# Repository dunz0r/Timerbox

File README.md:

Timerbox
========

A small AVR-controlled timerbox

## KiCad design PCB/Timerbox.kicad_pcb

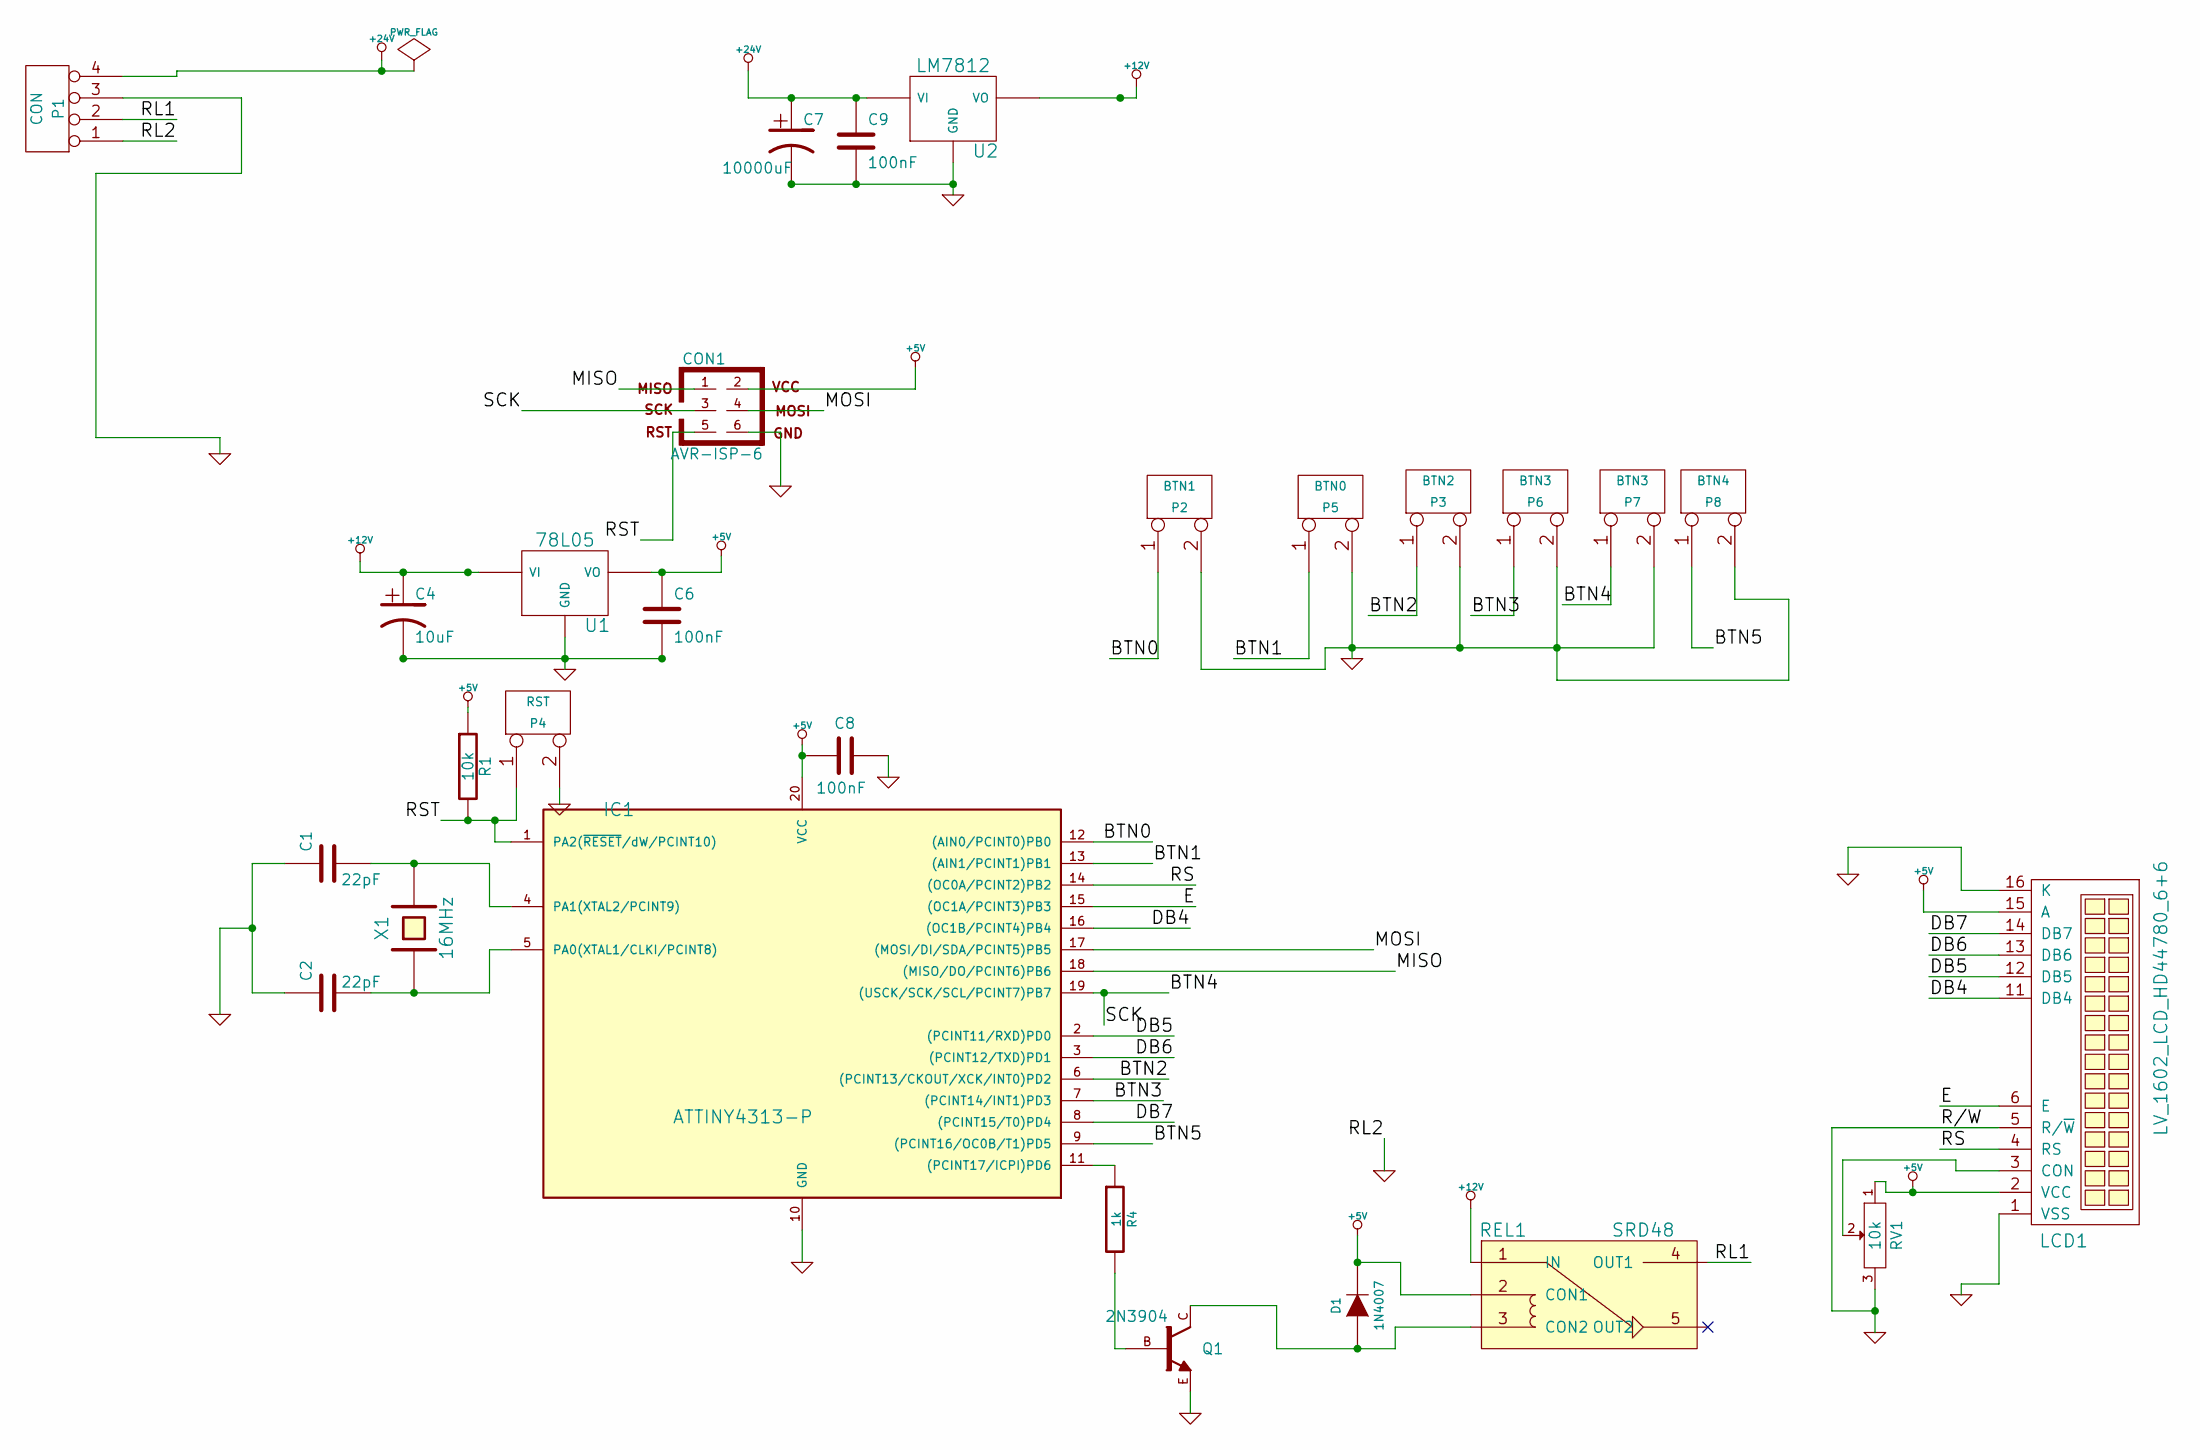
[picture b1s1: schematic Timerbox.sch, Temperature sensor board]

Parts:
C1, C2: 22pF
C4: 10uF
C6, C8, C9: 100nF
C7: 10000uF
CON1: AVR-ISP-6
D1: 1N4007
IC1: ATTINY4313-P; DIP20
LCD1: LV_1602_LCD_HD44780_6+6
P1: CON
P2: BTN1
P3: BTN2
P4: RST
P5: BTN0
P6, P7: BTN3
P8: BTN4
Q1: 2N3904
R1: 10k
R4: 1k
REL1: SRD48
RV1: 10k
U1: 78L05
U2: LM7812
X1: 16MHz

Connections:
+5V: C6.1, C8.1, CON1.2, D1.2 (K), IC1.20 (VCC), LCD1.2 (VCC), LCD1.15 (A), R1.1, REL1.2 (CON1), RV1.1, U1.VO
+12V: C4.1, REL1.1 (IN), U1.VI, U2.VO
+24V: C7.1, C9.1, P1.4, U2.VI
/BTN0: IC1.12 ((AIN0/PCINT0)PB0), P2.1
/BTN1: IC1.13 ((AIN1/PCINT1)PB1), P5.1
/BTN2: IC1.6 ((PCINT13/CKOUT/XCK/INT0)PD2), P3.1
/BTN3: IC1.7 ((PCINT14/INT1)PD3), P6.1
/BTN4: CON1.3, IC1.19 ((USCK/SCK/SCL/PCINT7)PB7), P7.1
/BTN5: IC1.9 ((PCINT16/OC0B/T1)PD5), P8.1
/DB4: IC1.16 ((OC1B/PCINT4)PB4), LCD1.11 (DB4)
/DB5: IC1.2 ((PCINT11/RXD)PD0), LCD1.12 (DB5)
/DB6: IC1.3 ((PCINT12/TXD)PD1), LCD1.13 (DB6)
/DB7: IC1.8 ((PCINT15/T0)PD4), LCD1.14 (DB7)
/E: IC1.15 ((OC1A/PCINT3)PB3), LCD1.6 (E)
/MISO: CON1.1, IC1.18 ((MISO/DO/PCINT6)PB6)
/MOSI: CON1.4, IC1.17 ((MOSI/DI/SDA/PCINT5)PB5)
/RL1: P1.2, REL1.4 (OUT1)
/RS: IC1.14 ((OC0A/PCINT2)PB2), LCD1.4 (RS)
/RST: CON1.5, IC1.1 (PA2(~RESET~/dW/PCINT10)), P4.1, R1.2
GND: C1.1, C2.1, C4.2, C6.2, C7.2, C8.2, C9.2, CON1.6, IC1.10 (GND), LCD1.1 (VSS), LCD1.5 (R/~W), LCD1.16 (K), P1.1, P1.3, P2.2 (PM), P3.2 (PM), P4.2 (PM), P5.2 (PM), P6.2 (PM), P7.2 (PM), P8.2 (PM), Q1.E, RV1.3, U1.GND, U2.GND
unnamed: IC1.11 ((PCINT17/ICPI)PD6), R4.1
unnamed: LCD1.3 (CON), RV1.2
unnamed: Q1.B, R4.2
unnamed: C1.2, IC1.4 (PA1(XTAL2/PCINT9)), X1.2
unnamed: C2.2, IC1.5 (PA0(XTAL1/CLKI/PCINT8)), X1.1
unnamed: D1.1 (A), Q1.C, REL1.3 (CON2)

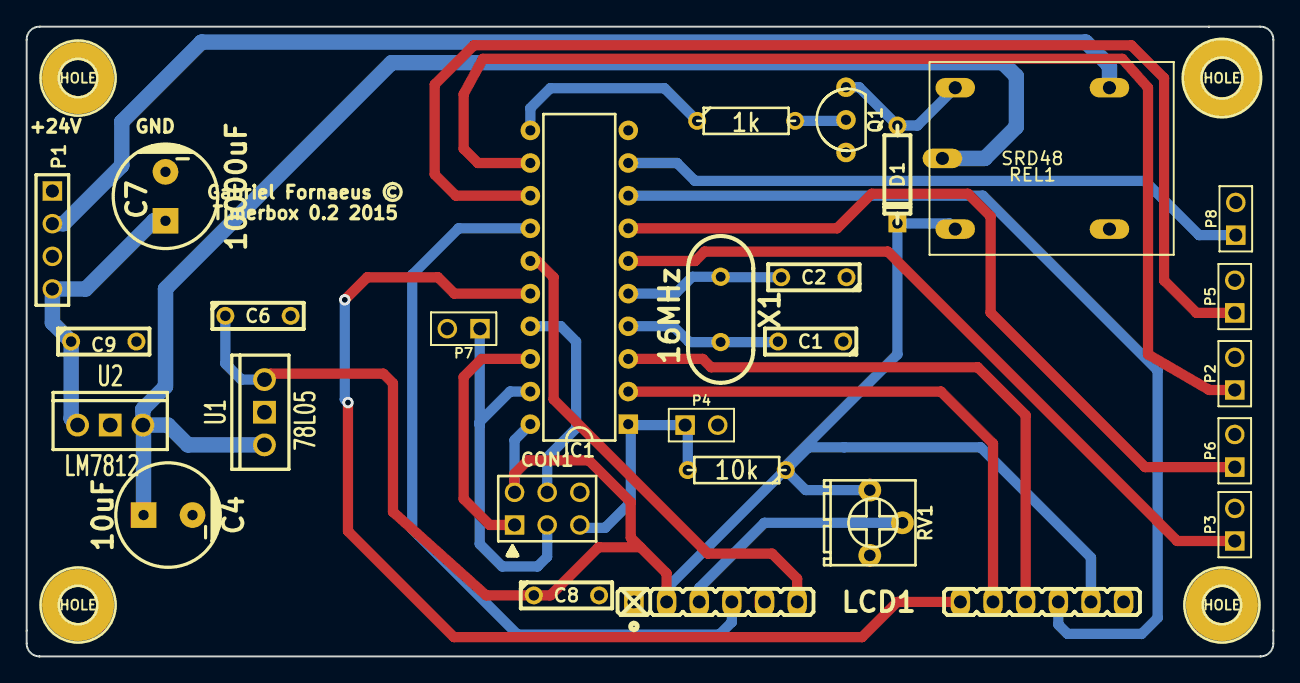
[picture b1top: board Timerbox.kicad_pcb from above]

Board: 2 copper layers, 97.0 x 49.0 mm, 31 parts (0 on the bottom side), 26 nets.

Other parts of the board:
HOLE: Val**; HOLE_30
HOLE#2, HOLE#3, HOLE#4: Val**; HOLE_28

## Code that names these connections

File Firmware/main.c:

/*
 * File Name : main.c
 * Purpose : Blink an LED
 * Creation Date : 01-05-2013
 * Last Modified : mån 15 sep 2014 23:47:50
 * Created By : Gabriel Fornaeus, <gf@hax0r.se>
 *
 */

#include <avr/io.h>
#include <util/delay.h>
#include <avr/interrupt.h>
#include <stdio.h>
#include "lib/buttons.h"
#include "lib/hd44780.h"

int main (void) {
	// Clear interrupts during setup phase
	cli();
	lcd_init();
	lcd_clrscr();
	lcd_gotoxy(0,1);
	lcd_puts("http://hax0r.se");
	// Set up as output
	DDRD |= (1 << PD5) | (1 << PD6);

	// Set up inputs
	DDRD &= ~(1 << PD2);
	DDRD &= ~(1 << PD3);
	// Enable pullups
	PORTD |= (1 << PD2);
	PORTD |= (1 << PD3);

	// initialize and enale interrupts
	initInterrupts();
	sei();

	// Go to zero position
	lcd_gotoxy(0,0);
	_delay_ms(1000);
	lcd_clrscr();
	for(;;) {
		PORTD ^= (1 << PD5);
		_delay_ms(200);
	}
}

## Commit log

2014-09-08 Gitignore and netlist
2014-09-15 Formatting edits
2014-09-15 Moved libraries
2014-09-15 Interrupts moved to library
2014-09-15 Interrupts library
2014-09-15 Clarifying comments
2014-09-15 Renamed interrupts to encoders
2014-09-15 Settings file for encoders added
2014-10-07 Makefile updated
2014-12-02 New PCB
2014-12-14 Buttons
2014-12-14 Clarifying comments, pullups
2014-12-14 Changes to lcd-handling, ugly debouncing
2015-04-29 Redid the pcb
2015-05-03 Changed contrast pot
